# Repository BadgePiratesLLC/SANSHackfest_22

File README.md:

# SANSHackfest_22
SANSHackfest_22

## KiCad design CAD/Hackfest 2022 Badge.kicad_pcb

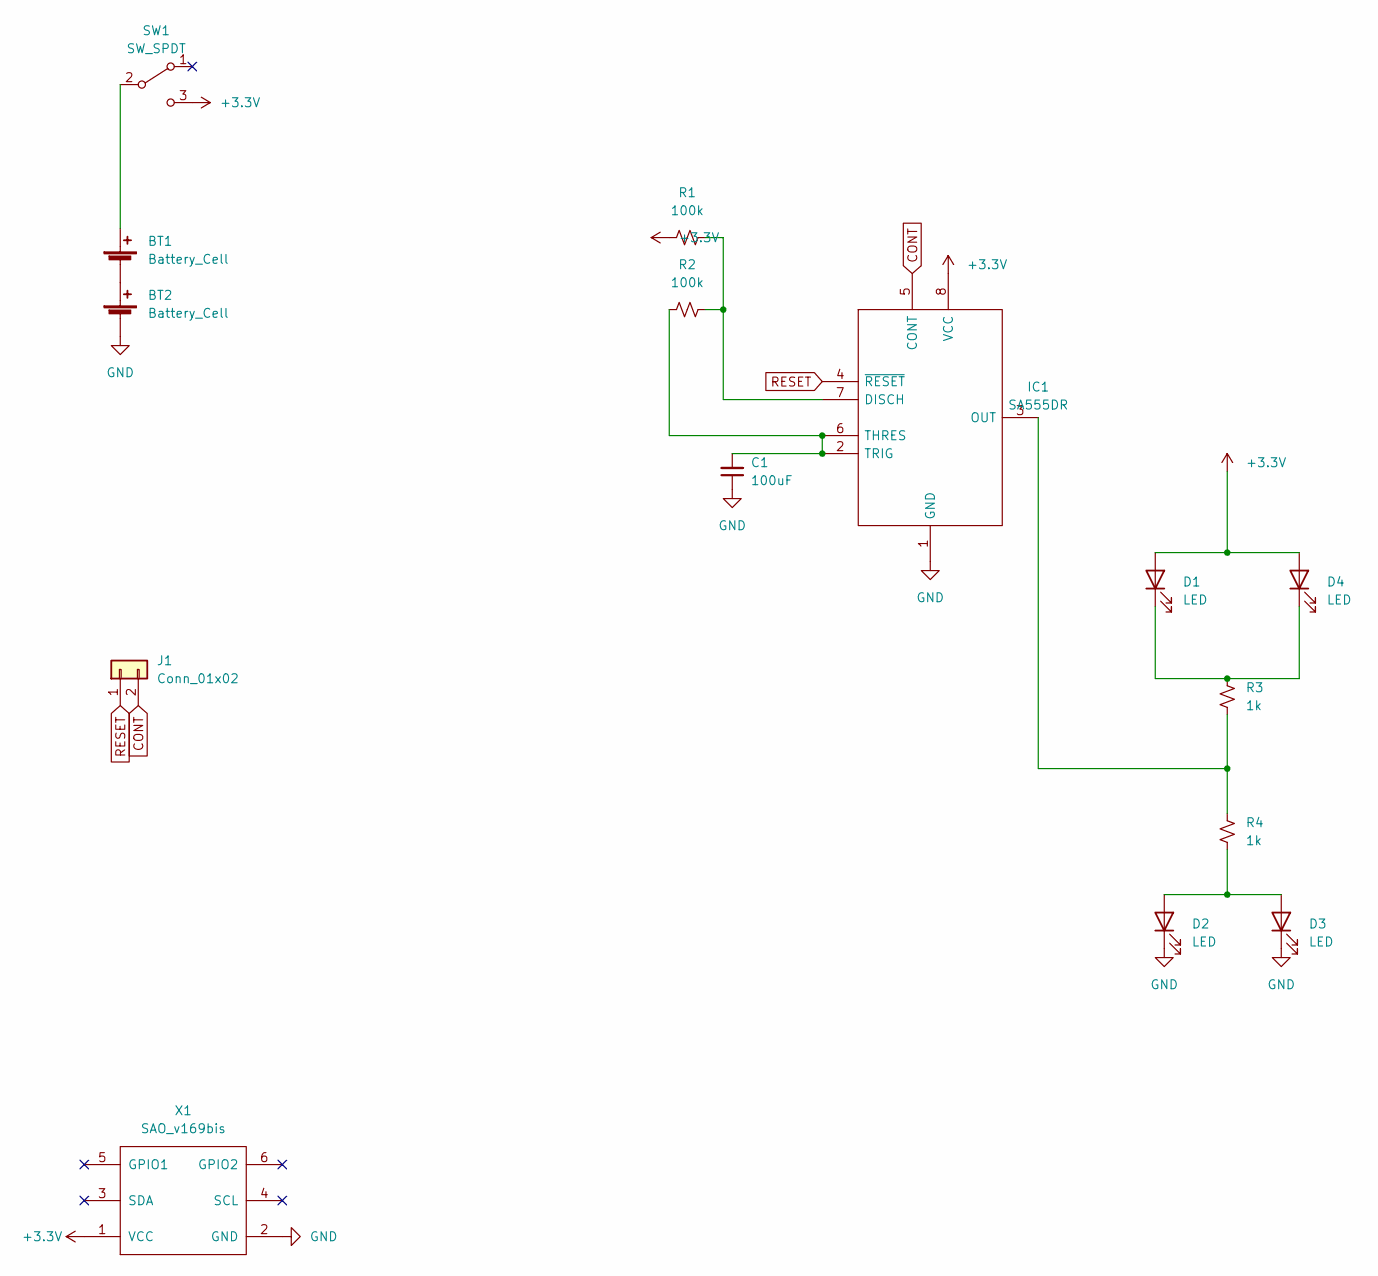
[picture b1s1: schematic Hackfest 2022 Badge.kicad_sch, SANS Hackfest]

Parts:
BT1, BT2: Battery_Cell; BatteryHolder_MPD_BC2003_1x2032_Fixed
C1: 100uF; C_0805_2012Metric
D1, D2, D3, D4: LED; LED_Osram_Lx_P47F_D2mm_ReverseMount_Proper_Mask Only
IC1: SA555DR; SOIC-8-1EP_W3.9mm; Manufacturer_Part_Number NE555DR; Mouser Part Number 595-NE555DR
J1: Conn_01x02; TestPoint_Pad_D2.0mm x2
R1, R2: 100k; R_1206_3216Metric
R3, R4: 1k; R_1206_3216Metric
SW1: SW_SPDT; SW_SPDT_PCM12
X1: SAO_v169bis; Badgelife-SAOv169-SAO_Side_B.SLK

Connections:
+3.3V: D1.2 (A), D4.2 (A), IC1.8 (VCC), R1.1, SW1.3 (C), X1.1 (VCC)
CONT: IC1.5 (CONT), J1.2
GND: BT2.2 (-), C1.1, D2.1 (K), D3.1 (K), IC1.1 (GND), X1.2 (GND)
unnamed: BT1.1 (+), SW1.2 (B)
unnamed: BT1.2 (-), BT2.1 (+)
unnamed: C1.2, IC1.2 (TRIG), IC1.6 (THRES), R2.1
unnamed: D1.1 (K), D4.1 (K), R3.1
unnamed: D2.2 (A), D3.2 (A), R4.2
unnamed: IC1.3 (OUT), R3.2, R4.1
unnamed: IC1.7 (DISCH), R1.2, R2.2
RESET: IC1.4 (~RESET), J1.1

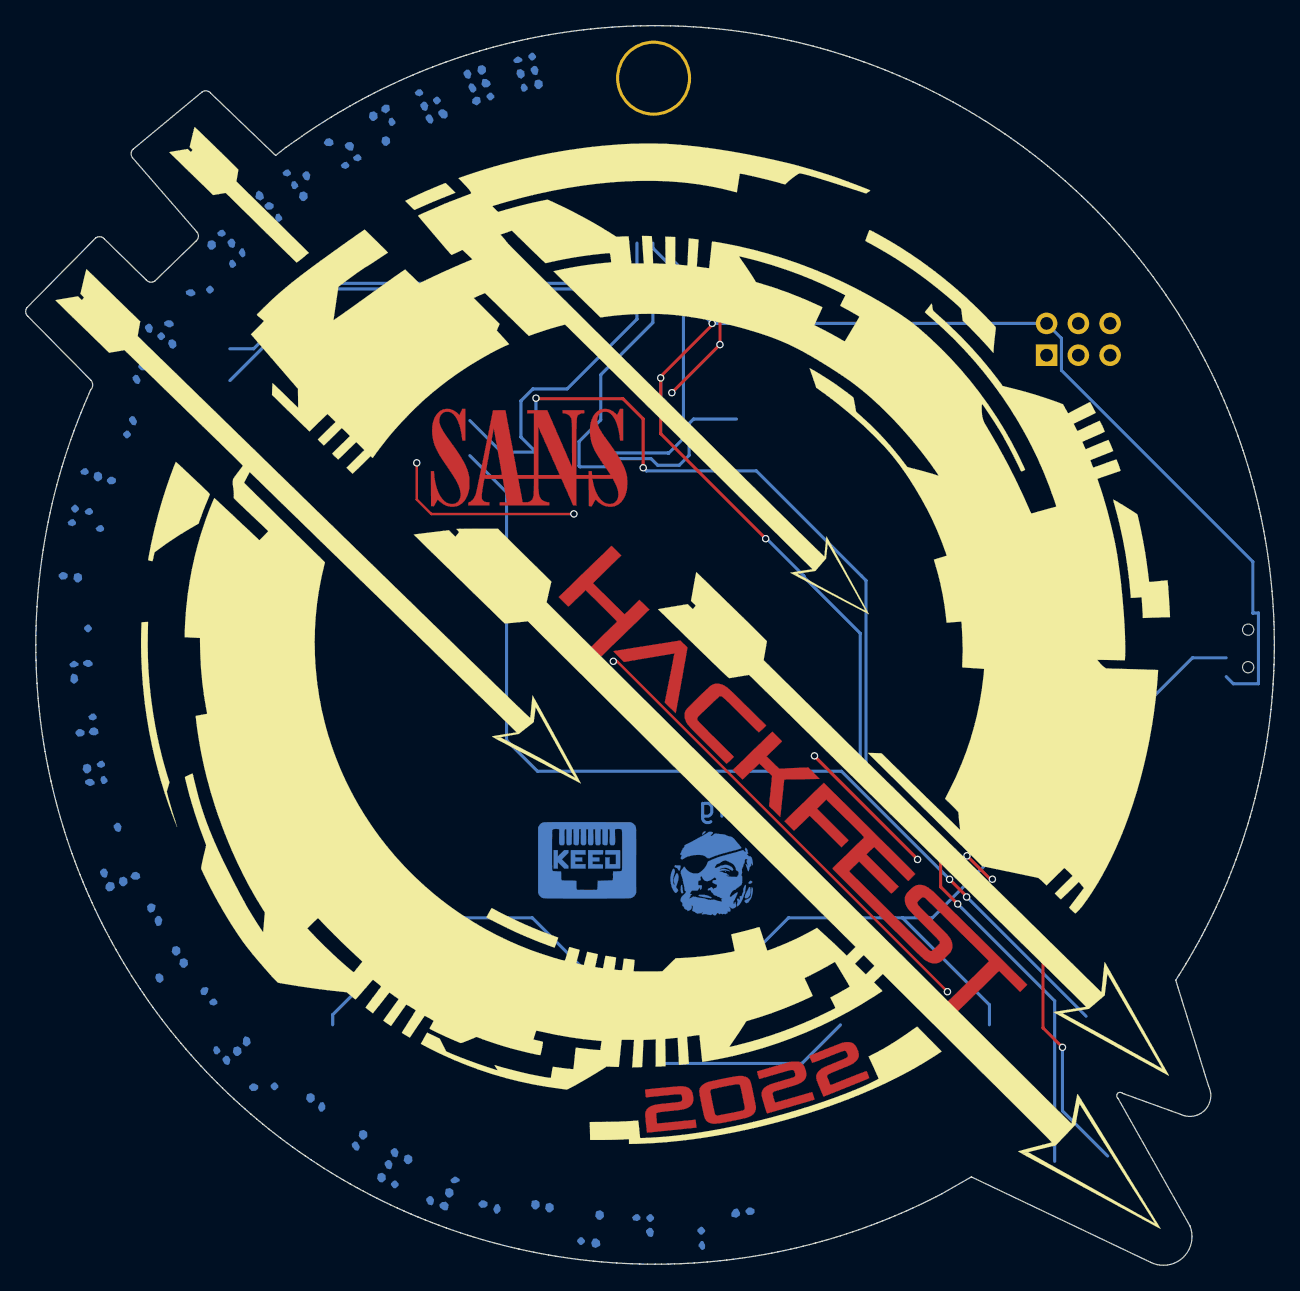
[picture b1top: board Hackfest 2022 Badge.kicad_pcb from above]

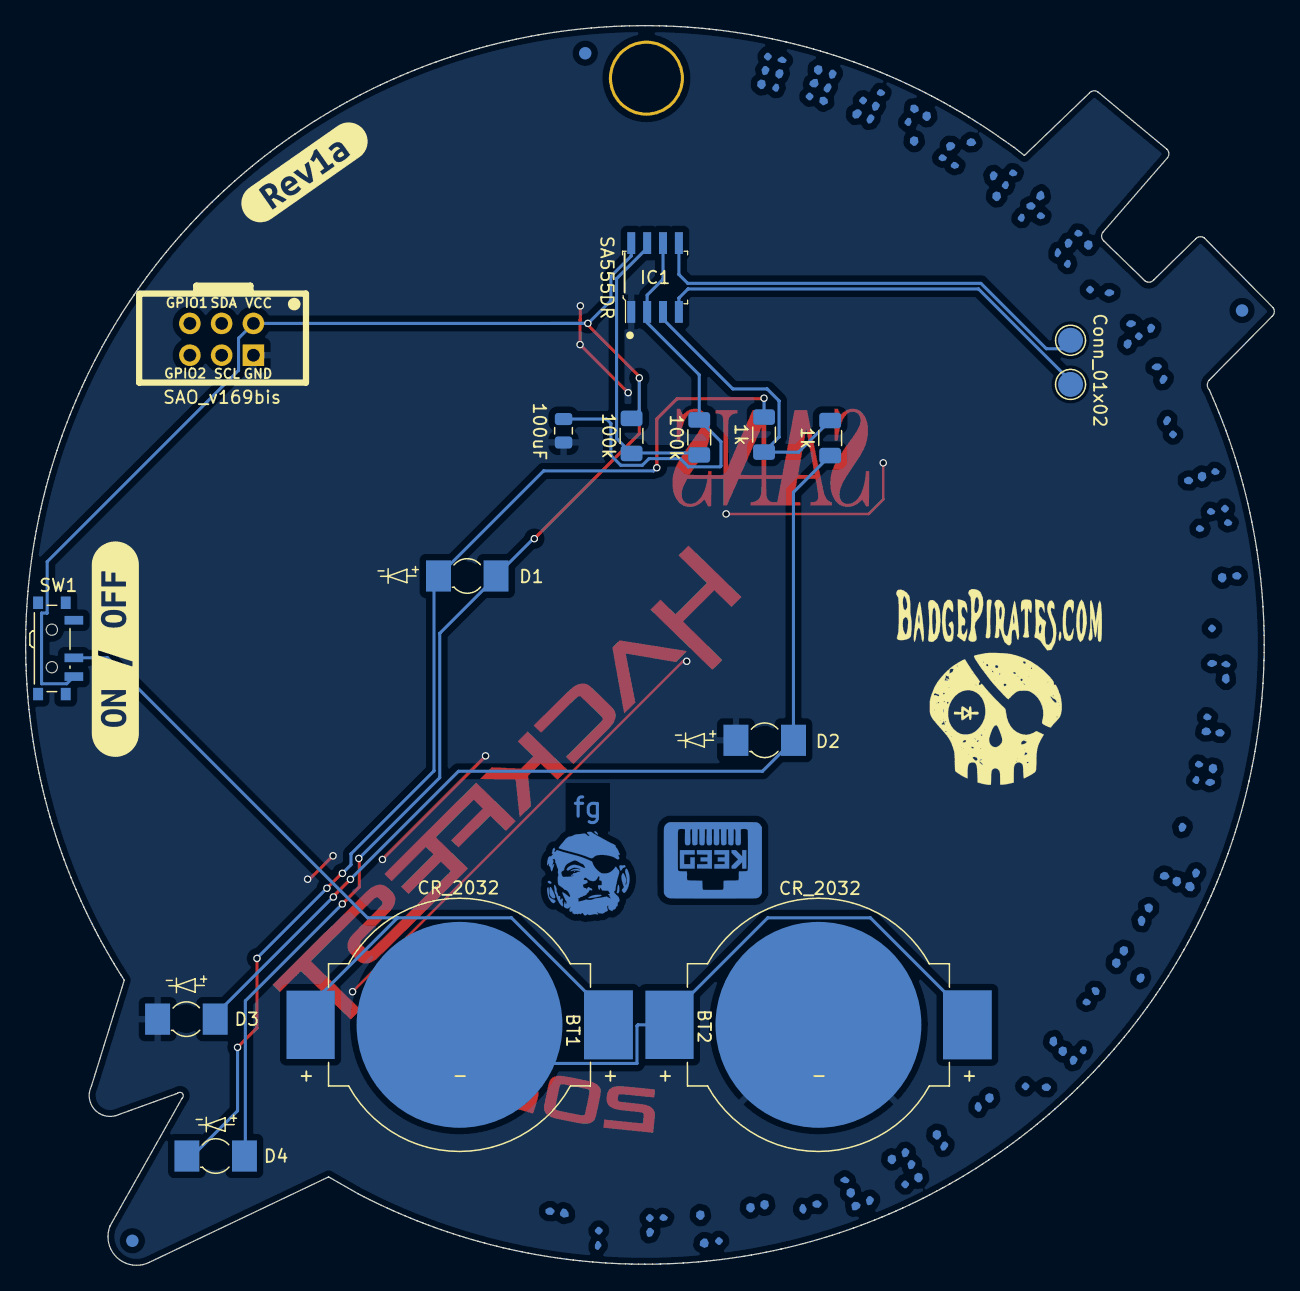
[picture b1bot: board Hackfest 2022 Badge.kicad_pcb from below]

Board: 2 copper layers, 99.8 x 99.1 mm, 17 parts (12 on the bottom side), 11 nets.

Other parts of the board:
kibuzzard-634AC14A: G***; kibuzzard-634AC14A
kibuzzard-634AC743: G***; kibuzzard-634AC743
